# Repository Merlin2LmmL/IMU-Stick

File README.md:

# IMU-Stick
# Hardware
## Use Cases
When thinking abiout a new Project I remembered my Studica Robot, that i assembled and wrote software for. I was currently on the way of developing SLAM for the Robot using a LiDAR Sensor to allow for automomos sloving of tasks in the Robo Cup. I remembered, that pseudo IMU data can be generated using the cmd_vel ROS2 topic but those are often very unreliable due to drifting. That lead to the idea of buying a IMU Sensor. But what's better than buying someting? Correct! Building it yourself! So I began to think about what form factor I wanted the sensor to be. I figured that there is no real benefit of thinking about where to place the Sensor, since the motion is everywhere the same inside the robot so i chose the smallest possible form factor: Plugging the Sensor right into the Raspberry Pi 5, thats powering the Robot.

## Components
### Chip
For a chip I chose the all mighty rp2040 since its very easy to use and very popular. I obviously couldn't use an entire microcontroller like the rp zero or the XIOA rp2040, because they all already have a USB Port, which is useless for me and there is no microcontroller with a USB A Plug.

### USB Interface
Since the Sensor is going to be plugged into a Raspberry Pi 5, the only real option is USB A, because all the IO ports are occupied by the HAT that powers the Motorcontroller. USB A would also allow for universal use with basically any device. I concluded to USB 2.0 since 3. would be ovekill and only elevate the price of the PCB.

### IMU Senor
I decided to use the ICM-45686 in Single Interface Mode (SPI Interface to Host) since it is fits here really well and allows me to easily communicate with the Sensor over SPI and make programming the firmware later easier.

### Flash Memory
Since we're using a bare chip here, we obviously need flash memory to store the firmware onto it. There is not really much to say on why i settled for the W25Q128JVS because there are no real differences in Flash Memories.

## Pictures
### Schematic: 

### PCB

### Case

Also Note, that I purposely added a clutch powered way to open and close the Case. I plan on maybe gluing the top and bottom part of the case together, if they end up not having enough clutching power, because there is no real need in opening the case.

# Software
## Firmware
I wrote some Firmware for the Stick to send the motion data to the device its plugged in. Acess the firmware here: "firmware/imu_usb.c"

## Software use
Now to read the Sensor data, there are mltiple options. One is to immediately recieve the data via the terminal by executing this bash command:
```bash
screen /dev/ttyACM0 115200
```
or
```bash
cat /dev/ttyACM0
```
Another way would be to use a simple python script to read out the data like so:
```python
import serial

ser = serial.Serial('/dev/ttyACM0', 115200)

while True:
    line = ser.readline().decode().strip()
    ax, ay, az, gx, gy, gz = map(int, line.split(','))
    print(ax, ay, az, gx, gy, gz)
```
And using that same principle you can also publish the data onto a ROS2 topich, which is the way that I'm going to use it.

# BOM.csv
| Name | Total Cost | Quantity |
|-----------------|-----------|---|
| PCB + Assembly + Parts | $81.84 | 5 |
| ICM45686 | $5.91 | 1 |

Total Price: 87.75$

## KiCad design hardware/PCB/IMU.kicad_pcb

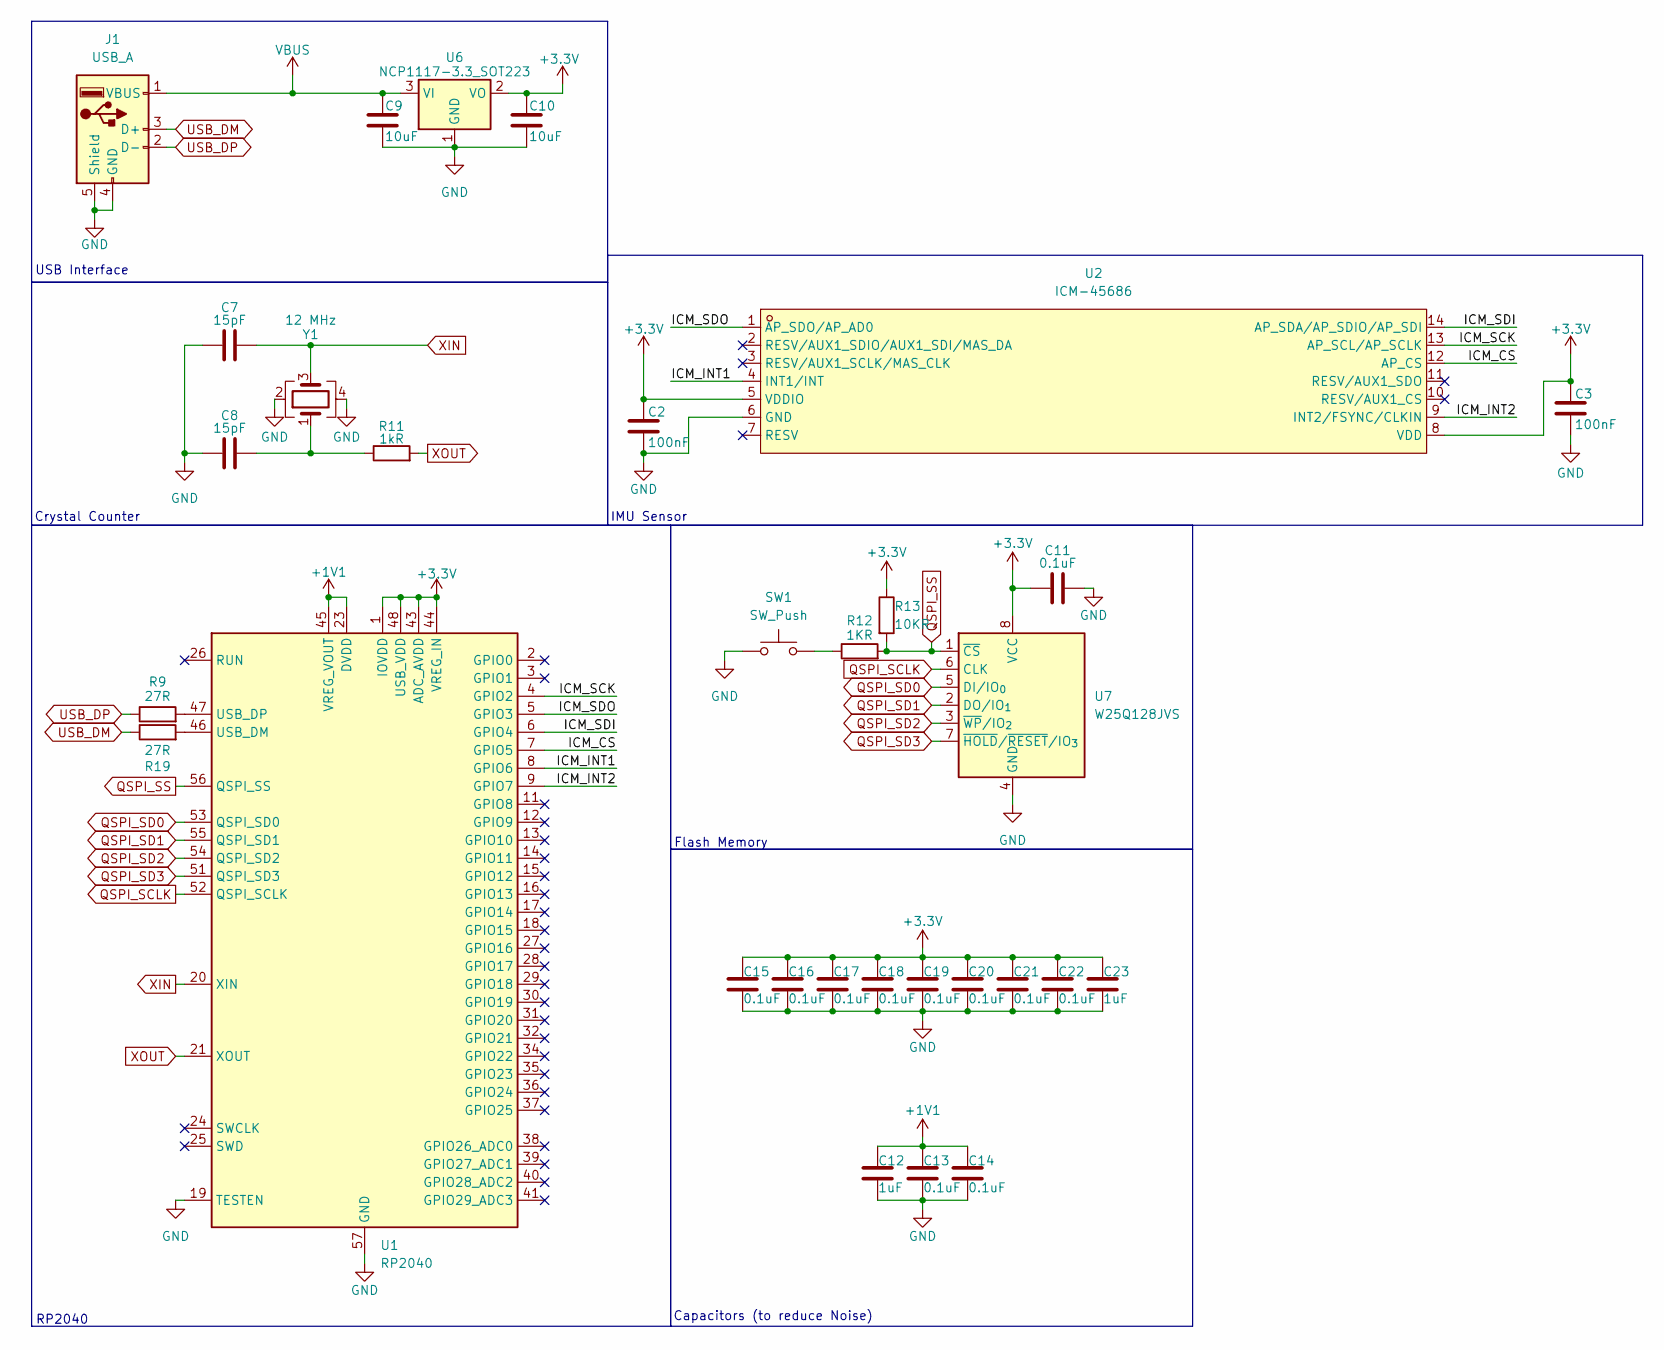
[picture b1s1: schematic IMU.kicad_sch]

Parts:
C2, C3: 100nF; C_0603_1608Metric_Pad1.08x0.95mm_HandSolder
C7, C8: 15pF; C_0603_1608Metric_Pad1.08x0.95mm_HandSolder
C9, C10: 10uF; C_0603_1608Metric_Pad1.08x0.95mm_HandSolder
C11, C13, C14, C15, C16, C17, C18, C19, C20, C21, C22: 0.1uF; C_0603_1608Metric_Pad1.08x0.95mm_HandSolder
C12, C23: 1uF; C_0603_1608Metric_Pad1.08x0.95mm_HandSolder
J1: USB_A; USB_A_CNCTech_1001-011-01101_Horizontal
R9, R19: 27R; R_0603_1608Metric_Pad0.98x0.95mm_HandSolder
R11: 1kR; R_0603_1608Metric_Pad0.98x0.95mm_HandSolder
R12: 1KR; R_0603_1608Metric_Pad0.98x0.95mm_HandSolder
R13: 10KR; R_0603_1608Metric_Pad0.98x0.95mm_HandSolder
SW1: SW_Push; SW_Push_SPST_NO_Alps_SKRK
U1: RP2040; QFN-56-1EP_7x7mm_P0.4mm_EP3.2x3.2mm
U2: ICM-45686; LGA-14_L3.0-W2.5-P0.50-TL; LCSC Part C22459454
U6: NCP1117-3.3_SOT223; SOT-223-3_TabPin2
U7: W25Q128JVS; SOIC-8_5.3x5.3mm_P1.27mm
Y1: 12 MHz; Crystal_SMD_SeikoEpson_TSX3225-4Pin_3.2x2.5mm

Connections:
+1V1: C12.1, C13.1, C14.1, U1.23 (DVDD), U1.45 (VREG_VOUT), U1.50 (DVDD)
+3.3V: C2.1, C3.1, C10.1, C11.1, C15.1, C16.1, C17.1, C18.1, C19.1, C20.1, C21.1, C22.1, C23.1, R13.1, U1.1 (IOVDD), U1.10 (IOVDD), U1.22 (IOVDD), U1.33 (IOVDD), U1.42 (IOVDD), U1.43 (ADC_AVDD), U1.44 (VREG_IN), U1.48 (USB_VDD), U1.49 (IOVDD), U2.5 (VDDIO), U2.8 (VDD), U6.2 (VO), U7.8 (VCC)
/ICM_CS: U1.7 (GPIO5), U2.12 (AP_CS)
/ICM_INT1: U1.8 (GPIO6), U2.4 (INT1/INT)
/ICM_INT2: U1.9 (GPIO7), U2.9 (INT2/FSYNC/CLKIN)
/ICM_SCK: U1.4 (GPIO2), U2.13 (AP_SCL/AP_SCLK)
/ICM_SDI: U1.6 (GPIO4), U2.14 (AP_SDA/AP_SDIO/AP_SDI)
/ICM_SDO: U1.5 (GPIO3), U2.1 (AP_SDO/AP_AD0)
GND: C2.2, C3.2, C7.1, C8.1, C9.2, C10.2, C11.2, C12.2, C13.2, C14.2, C15.2, C16.2, C17.2, C18.2, C19.2, C20.2, C21.2, C22.2, C23.2, J1.4 (GND), J1.5 (Shield), SW1.1, U1.19 (TESTEN), U1.57 (GND), U2.6 (GND), U6.1 (GND), U7.4 (GND), Y1.2, Y1.4
unnamed: C8.2, R11.1, Y1.1
unnamed: R12.1, SW1.2
unnamed: R19.2, U1.46 (USB_DM)
unnamed: R9.2, U1.47 (USB_DP)
QSPI_SCLK: U1.52 (QSPI_SCLK), U7.6 (CLK)
QSPI_SD0: U1.53 (QSPI_SD0), U7.5 (DI/IO_{0})
QSPI_SD1: U1.55 (QSPI_SD1), U7.2 (DO/IO_{1})
QSPI_SD2: U1.54 (QSPI_SD2), U7.3 (~WP/IO_{2})
QSPI_SD3: U1.51 (QSPI_SD3), U7.7 (~HOLD/~RESET/IO_{3})
QSPI_SS: R12.2, R13.2, U1.56 (QSPI_SS), U7.1 (~CS)
USB_DM: J1.3 (D+), R19.1
USB_DP: J1.2 (D-), R9.1
VBUS: C9.1, J1.1 (VBUS), U6.3 (VI)
XIN: C7.2, U1.20 (XIN), Y1.3
XOUT: R11.2, U1.21 (XOUT)

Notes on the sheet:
Flash Memory
Crystal Counter
IMU Sensor
USB Interface
RP2040
Capacitors (to reduce Noise)

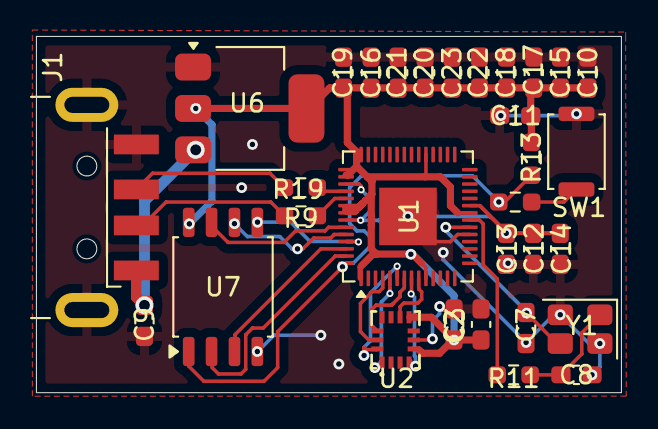
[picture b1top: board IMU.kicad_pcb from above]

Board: 2 copper layers, 32.5 x 19.8 mm, 31 parts (0 on the bottom side), 24 nets.

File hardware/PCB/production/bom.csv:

Designator,Footprint,Quantity,Value,LCSC Part #
"C10, C9",0603,2,10uF,
"C11, C13, C14, C15, C16, C17, C18, C19, C20, C21, C22",0603,11,0.1uF,
"C12, C23",0603,2,1uF,
"C2, C3",0603,2,100nF,
"C7, C8",0603,2,15pF,
J1,USB_A_CNCTech_1001-011-01101_Horizontal,1,USB_A,
"R11, R12",0603,2,1kR,
R13,0603,1,10KR,
"R19, R9",0603,2,27R,
SW1,SW_Push_SPST_NO_Alps_SKRK,1,SW_Push,
U1,QFN-56-1EP_7x7mm_P0.4mm_EP3.2x3.2mm,1,RP2040,
U2,LGA-14_L3.0-W2.5-P0.50-TL,1,ICM-45686,C22459454
U6,SOT-223-3_TabPin2,1,NCP1117-3.3_SOT223,
U7,SOIC-8_5.3x5.3mm_P1.27mm,1,W25Q128JVS,
Y1,Crystal_SMD_SeikoEpson_TSX3225-4Pin_3.2x2.5mm,1,12 MHz,

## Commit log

2026-01-05 Added all kiCAD files
2026-01-05 Enhance README with hardware and software details
    Expanded the README with detailed hardware and software sections, including use cases, components, firmware, and BOM.
2026-01-05 Revise BOM table and include total cost
    Updated BOM table format and added total cost.
2026-01-22 Reworked PCB
    Moved Decoupeling Capacitors physically closer to buck converter and RP2040.
2026-01-22 Updated Picture for PCB
